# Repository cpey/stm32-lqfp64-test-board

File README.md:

# STM32 LQFP64 Test Board

A test board designed for STM32 microcontrollers in LQFP64 package. It is intended for use with the STM32F3 and STM32F0 64-pin MCUs, which are mostly pin-to-pin compatbile. The board is programmable via JTAG and SWD using the [STLINK-V3MINIE](https://www.st.com/en/development-tools/stlink-v3minie.html) programmer.

Check out the [schematic](https://github.com/cpey/stm32-lqfp64-test-board/blob/main/stm32_lqfp64_test_board/stm32_lqfp64_test_board.pdf) and the MCU [pin configuration](https://github.com/cpey/stm32-lqfp64-test-board/blob/main/pinout) for more details.

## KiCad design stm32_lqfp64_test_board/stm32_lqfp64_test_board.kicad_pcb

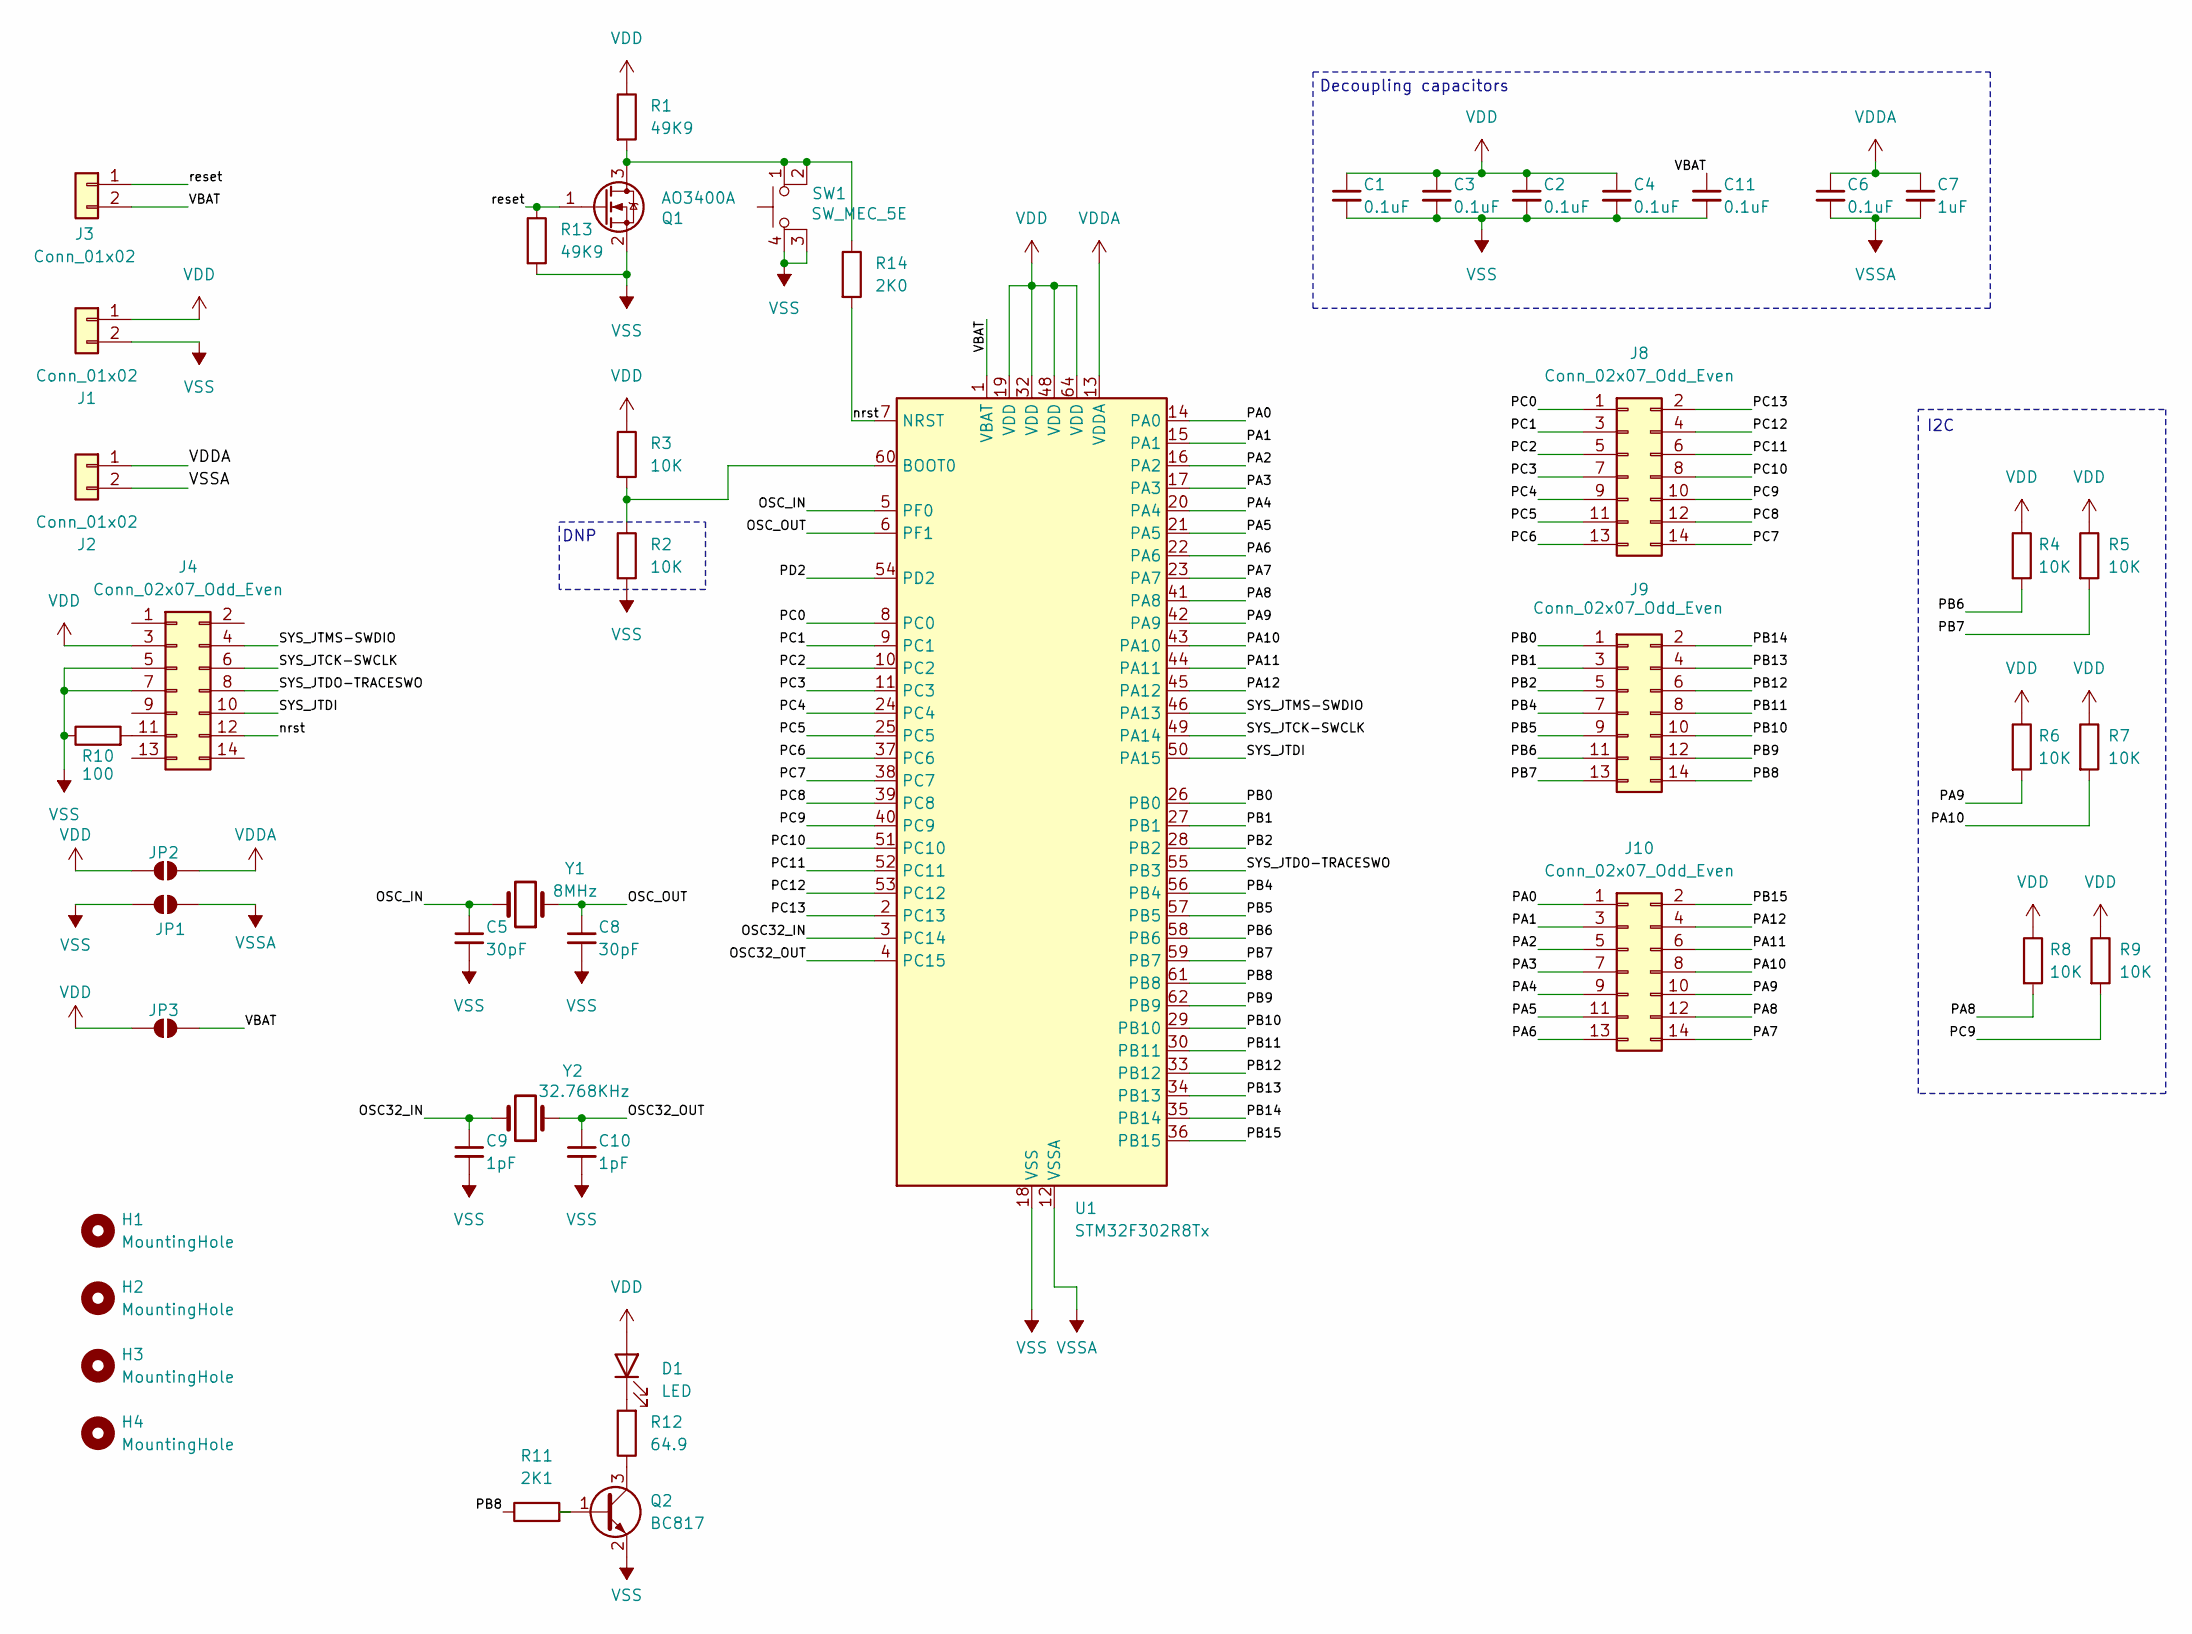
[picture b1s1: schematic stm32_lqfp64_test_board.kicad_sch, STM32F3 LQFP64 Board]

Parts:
C1, C2, C3, C4, C6, C11: 0.1uF; C_0805_2012Metric
C5, C8: 30pF; C_0805_2012Metric
C7: 1uF; C_0805_2012Metric
C9, C10: 1pF; C_0805_2012Metric
D1: LED; LED_0805_2012Metric
H1, H2, H3, H4: MountingHole; MountingHole_3.2mm_M3_Pad_TopBottom
J1, J2, J3: Conn_01x02; PinHeader_1x02_P2.54mm_Vertical
J4: Conn_02x07_Odd_Even; PinHeader_2x07_P1.27mm_Vertical_SMD
J8, J9, J10: Conn_02x07_Odd_Even; PinHeader_2x07_P2.54mm_Vertical
JP1, JP2, JP3: SolderJumper_2_Open; SolderJumper-2_P1.3mm_Open_RoundedPad1.0x1.5mm
Q1: AO3400A; SOT-23
Q2: BC817; SOT-23
R1, R13: 49K9; R_0805_2012Metric
R2, R3, R4, R5, R6, R7, R8, R9: 10K; R_0805_2012Metric
R10: 100; R_0805_2012Metric
R11: 2K1; R_0805_2012Metric
R12: 64.9; R_0805_2012Metric
R14: 2K0; R_0805_2012Metric
SW1: SW_MEC_5E; SW_SPST_PTS647_Sx38_2
U1: STM32F302R8Tx; LQFP-64_10x10mm_P0.5mm
Y1: 8MHz; Crystal_SMD_HC49-SD_FOX_FC4SD
Y2: 32.768KHz; Crystal_AT310_D2.4mm_L6.0mm_Horizontal_CFS-206

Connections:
/OSC32_IN: C9.1, U1.3 (PC14), Y2.2
/OSC32_OUT: C10.1, U1.4 (PC15), Y2.1
/OSC_IN: C5.1, U1.5 (PF0), Y1.2
/OSC_OUT: C8.1, U1.6 (PF1), Y1.1
/PA0: J10.1, U1.14 (PA0)
/PA1: J10.3, U1.15 (PA1)
/PA2: J10.5, U1.16 (PA2)
/PA3: J10.7, U1.17 (PA3)
/PA4: J10.9, U1.20 (PA4)
/PA5: J10.11, U1.21 (PA5)
/PA6: J10.13, U1.22 (PA6)
/PA7: J10.14, U1.23 (PA7)
/PA8: J10.12, R8.2, U1.41 (PA8)
/PA9: J10.10, R6.2, U1.42 (PA9)
/PA10: J10.8, R7.2, U1.43 (PA10)
/PA11: J10.6, U1.44 (PA11)
/PA12: J10.4, U1.45 (PA12)
/PB0: J9.1, U1.26 (PB0)
/PB1: J9.3, U1.27 (PB1)
/PB2: J9.5, U1.28 (PB2)
/PB4: J9.7, U1.56 (PB4)
/PB5: J9.9, U1.57 (PB5)
/PB6: J9.11, R4.2, U1.58 (PB6)
/PB7: J9.13, R5.2, U1.59 (PB7)
/PB8: J9.14, R11.1, U1.61 (PB8)
/PB9: J9.12, U1.62 (PB9)
/PB10: J9.10, U1.29 (PB10)
/PB11: J9.8, U1.30 (PB11)
/PB12: J9.6, U1.33 (PB12)
/PB13: J9.4, U1.34 (PB13)
/PB14: J9.2, U1.35 (PB14)
/PB15: J10.2, U1.36 (PB15)
/PC0: J8.1, U1.8 (PC0)
/PC1: J8.3, U1.9 (PC1)
/PC2: J8.5, U1.10 (PC2)
/PC3: J8.7, U1.11 (PC3)
/PC4: J8.9, U1.24 (PC4)
/PC5: J8.11, U1.25 (PC5)
/PC6: J8.13, U1.37 (PC6)
/PC7: J8.14, U1.38 (PC7)
/PC8: J8.12, U1.39 (PC8)
/PC9: J8.10, R9.2, U1.40 (PC9)
/PC10: J8.8, U1.51 (PC10)
/PC11: J8.6, U1.52 (PC11)
/PC12: J8.4, U1.53 (PC12)
/PC13: J8.2, U1.2 (PC13)
/PD2: U1.54 (PD2)
/SYS_JTCK-SWCLK: J4.6, U1.49 (PA14)
/SYS_JTDI: J4.10, U1.50 (PA15)
/SYS_JTDO-TRACESWO: J4.8, U1.55 (PB3)
/SYS_JTMS-SWDIO: J4.4, U1.46 (PA13)
/VBAT: C11.1, J3.2, JP3.1 (A), U1.1 (VBAT)
/nrst: J4.12, R14.2, U1.7 (NRST)
/reset: J3.1, Q1.1 (G), R13.1
unnamed: D1.1 (K), R12.2
unnamed: J4.11, R10.2
unnamed: Q1.3 (D), R1.2, R14.1, SW1.1, SW1.2
unnamed: Q2.1 (B), R11.2
unnamed: Q2.3 (C), R12.1
unnamed: R2.1, R3.2, U1.60 (BOOT0)
VDD: C1.1, C2.1, C3.1, C4.1, D1.2 (A), J1.1, J4.3, JP2.2 (B), JP3.2 (B), R1.1, R3.1, R4.1, R5.1, R6.1, R7.1, R8.1, R9.1, U1.19 (VDD), U1.32 (VDD), U1.48 (VDD), U1.64 (VDD)
VDDA: C6.1, C7.1, J2.1, JP2.1 (A), U1.13 (VDDA)
VSS: C1.2, C2.2, C3.2, C4.2, C5.2, C8.2, C9.2, C10.2, C11.2, J1.2, J4.5, J4.7, JP1.2 (B), Q1.2 (S), Q2.2 (E), R2.2, R10.1, R13.2, SW1.3 (K), SW1.4 (A), U1.18 (VSS), U1.31 (VSS), U1.47 (VSS), U1.63 (VSS)
VSSA: C6.2, C7.2, J2.2, JP1.1 (A), U1.12 (VSSA)

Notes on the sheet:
Decoupling capacitors
I2C
DNP

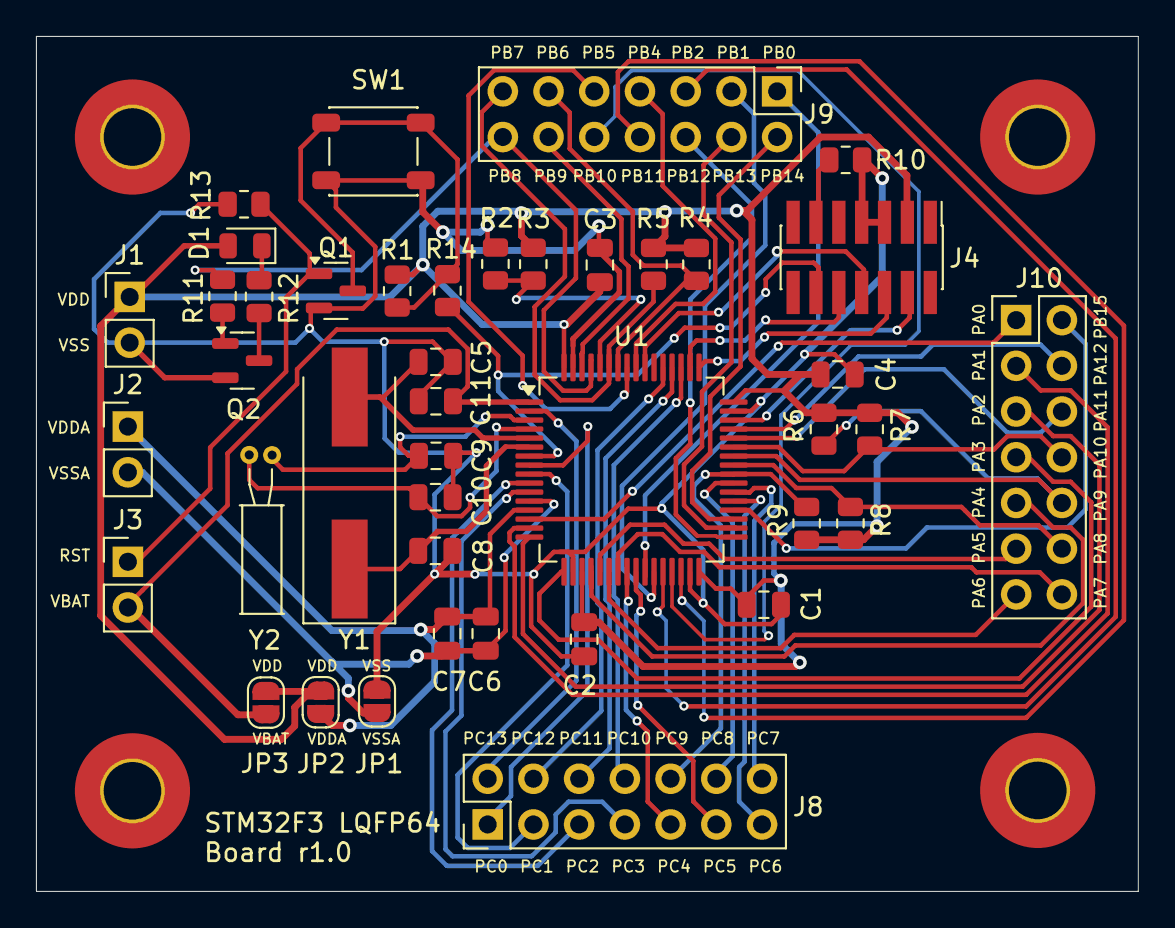
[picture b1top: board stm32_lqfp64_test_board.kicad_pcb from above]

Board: 2 copper layers, 61.2 x 47.5 mm, 46 parts (0 on the bottom side), 63 nets.

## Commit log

2024-12-07 Rev. 1.1
